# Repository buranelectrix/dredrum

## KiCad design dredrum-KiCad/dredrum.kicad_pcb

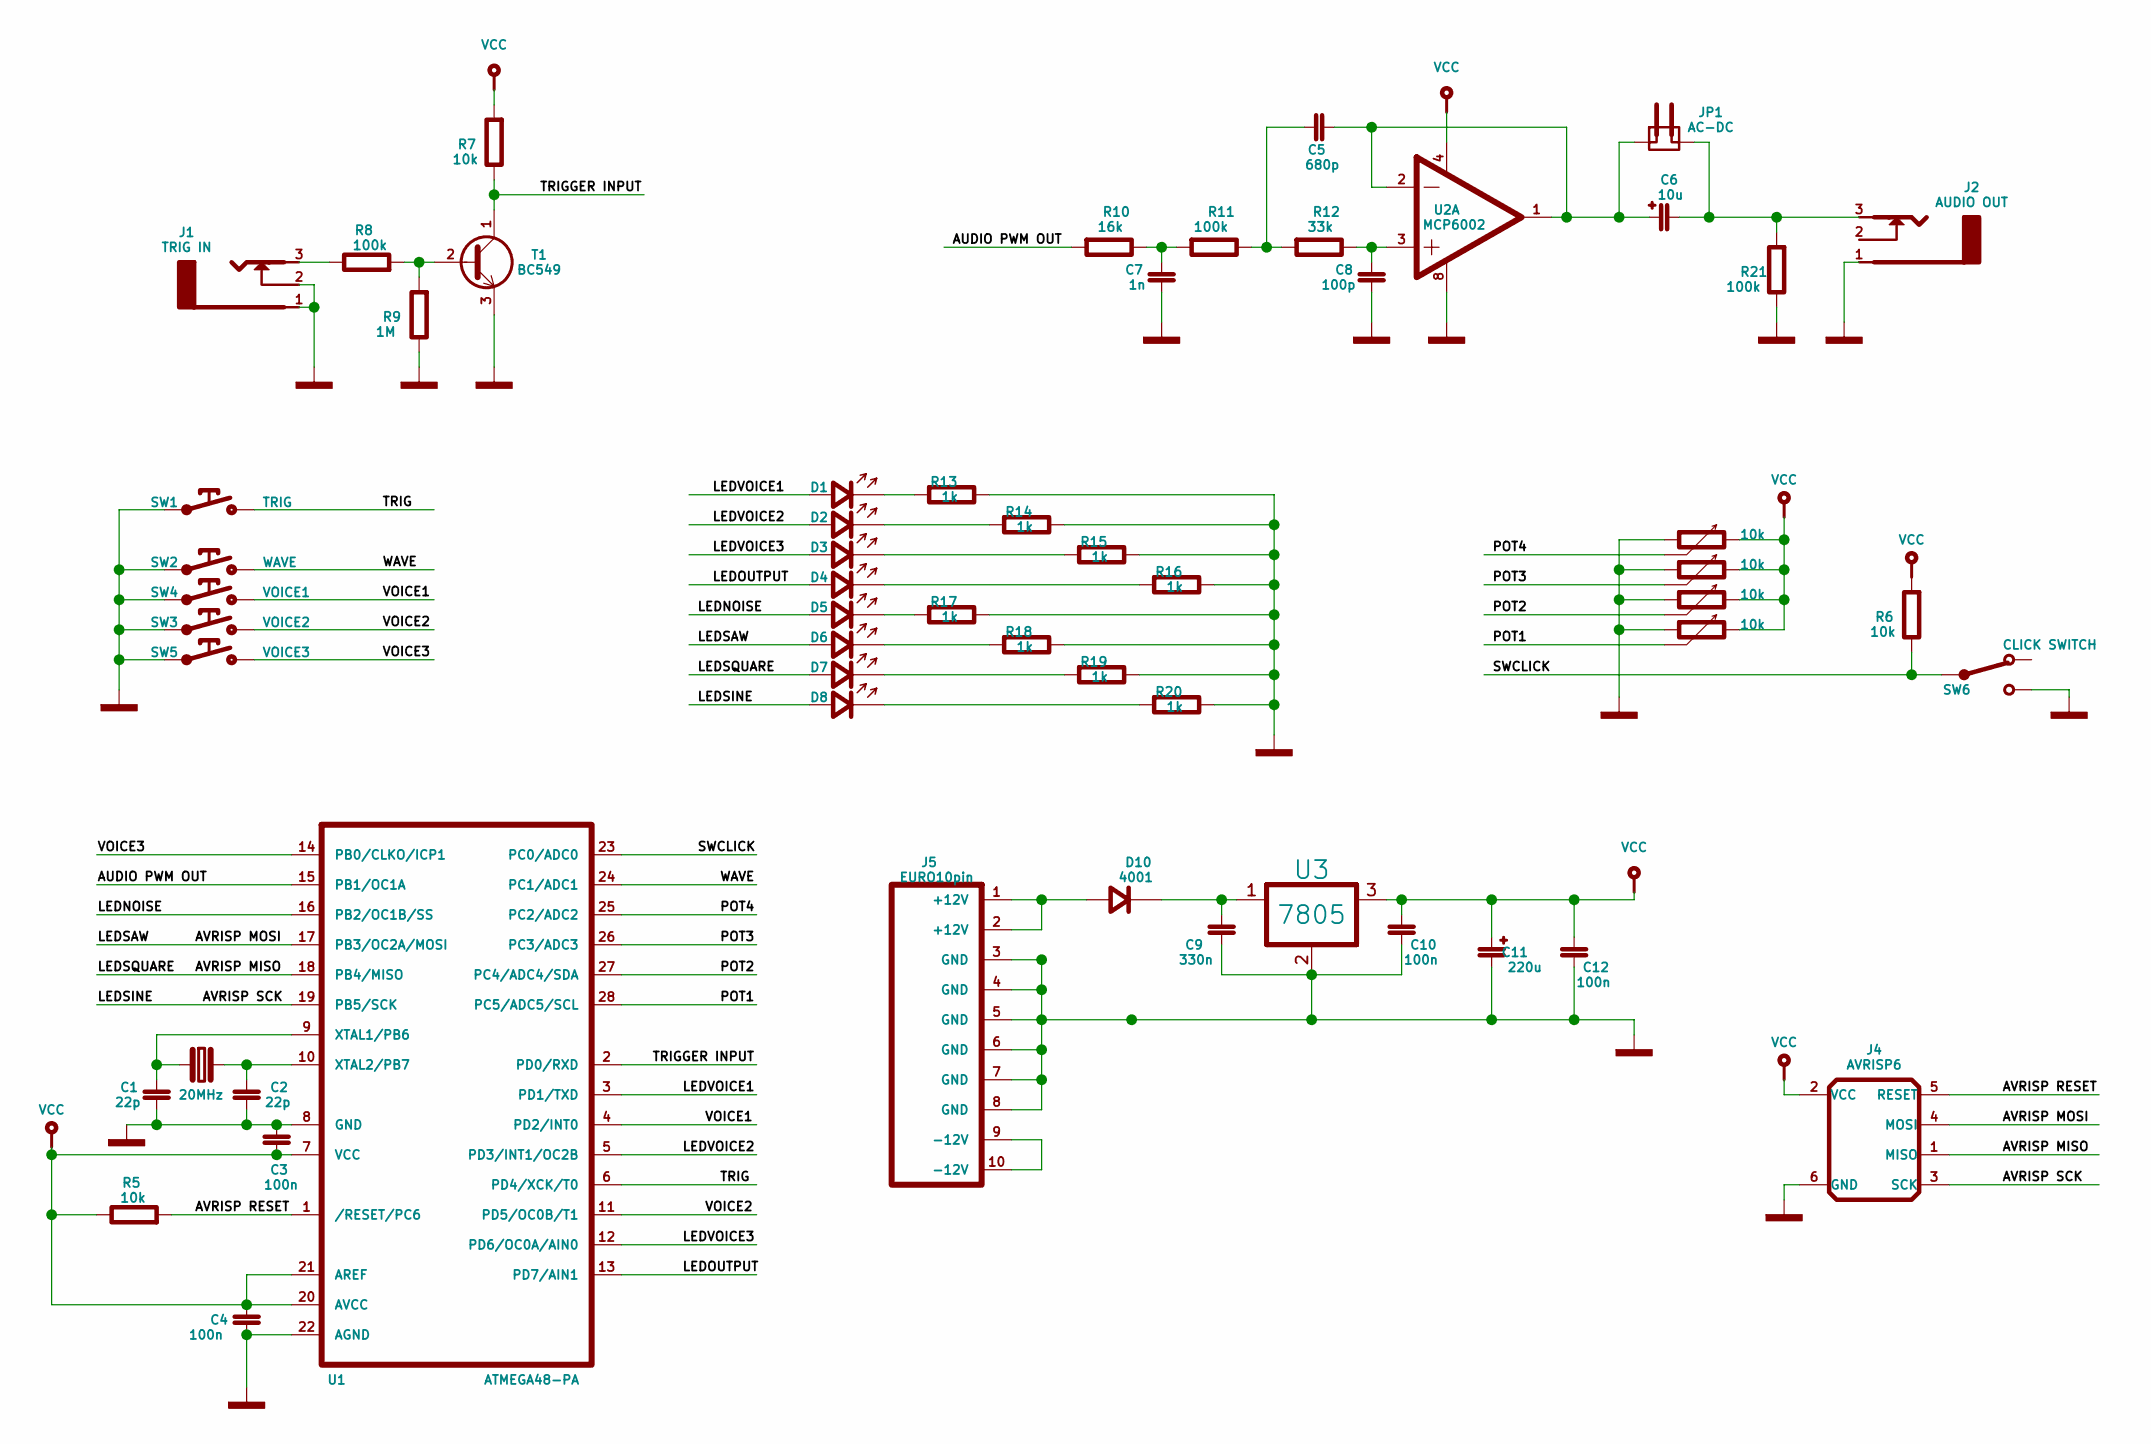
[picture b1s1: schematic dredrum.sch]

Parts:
C1, C2: 22p
C3, C4, C10, C12: 100n
C5: 680p
C6: 10u
C7: 1n
C8: 100p
C9: 330n
C11: 220u
D1: VOICE1
D2: VOICE2
D3: VOICE3
D4: OUTPUT
D5: NOISE
D6: SAW
D7: SQUARE
D8: SINE
D10: 4001
J1: TRIG IN
J2: AUDIO OUT
J4: AVRISP6
J5: EURO10pin
JP1: AC-DC
R1, R2, R3, R4, R5, R6, R7: 10k
R8, R11, R21: 100k
R9: 1M
R10: 16k
R12: 33k
R13, R14, R15, R16, R17, R18, R19, R20: 1k
SW1: TRIG
SW2: WAVE
SW3: VOICE2
SW4: VOICE1
SW5: VOICE3
SW6: CLICK SWITCH
T1: BC549
U1: ATMEGA48-PA
U2: MCP6002
U3: 7805
X?1: 20MHz

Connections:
/AUDIO PWM OUT: R10.1, U1.15 (PB1/OC1A)
/AVRISP MISO: D7.1, J4.1 (MISO), U1.18 (PB4/MISO)
/AVRISP MOSI: D6.1, J4.4 (MOSI), U1.17 (PB3/OC2A/MOSI)
/AVRISP RESET: J4.5 (RESET), R5.1, U1.1 (/RESET/PC6)
/AVRISP SCK: D8.1, J4.3 (SCK), U1.19 (PB5/SCK)
/LEDNOISE: D5.1, U1.16 (PB2/OC1B/SS)
/LEDOUTPUT: D4.1, U1.13 (PD7/AIN1)
/LEDVOICE1: D1.1, U1.3 (PD1/TXD)
/LEDVOICE2: D2.1, U1.5 (PD3/INT1/OC2B)
/LEDVOICE3: D3.1, U1.12 (PD6/OC0A/AIN0)
/POT1: R1.2, U1.28 (PC5/ADC5/SCL)
/POT2: R2.2, U1.27 (PC4/ADC4/SDA)
/POT3: R3.2, U1.26 (PC3/ADC3)
/POT4: R4.2, U1.25 (PC2/ADC2)
/SWCLICK: R6.2, SW6.2, U1.23 (PC0/ADC0)
/TRIG: SW1.2, U1.6 (PD4/XCK/T0)
/TRIGGER INPUT: R7.2, T1.1, U1.2 (PD0/RXD)
/VOICE1: SW4.2, U1.4 (PD2/INT0)
/VOICE2: SW3.2, U1.11 (PD5/OC0B/T1)
/VOICE3: SW5.2, U1.14 (PB0/CLKO/ICP1)
/WAVE: SW2.2, U1.24 (PC1/ADC1)
unnamed: D4.2, R16.1
unnamed: J1.3 (TIP), R8.2
unnamed: C9.2, D10.2, U3.1 (IN)
unnamed: D10.1, J5.1 (+12V), J5.2 (+12V)
unnamed: J5.9 (-12V), J5.10 (-12V)
unnamed: C1.2, U1.9 (XTAL1/PB6), X?1.1
unnamed: C2.2, U1.10 (XTAL2/PB7), X?1.2
unnamed: D8.2, R20.1
unnamed: D7.2, R19.1
unnamed: D6.2, R18.1
unnamed: D5.2, R17.1
unnamed: D3.2, R15.1
unnamed: D2.2, R14.1
unnamed: D1.2, R13.1
unnamed: C6.2, J2.3 (TIP), JP1.2, R21.1
unnamed: C5.2, C6.1, JP1.1, U2.1, U2.2
unnamed: R8.1, R9.1, T1.2
unnamed: C5.1, R11.2, R12.1
unnamed: C8.2, R12.2, U2.3
unnamed: C7.2, R10.2, R11.1

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
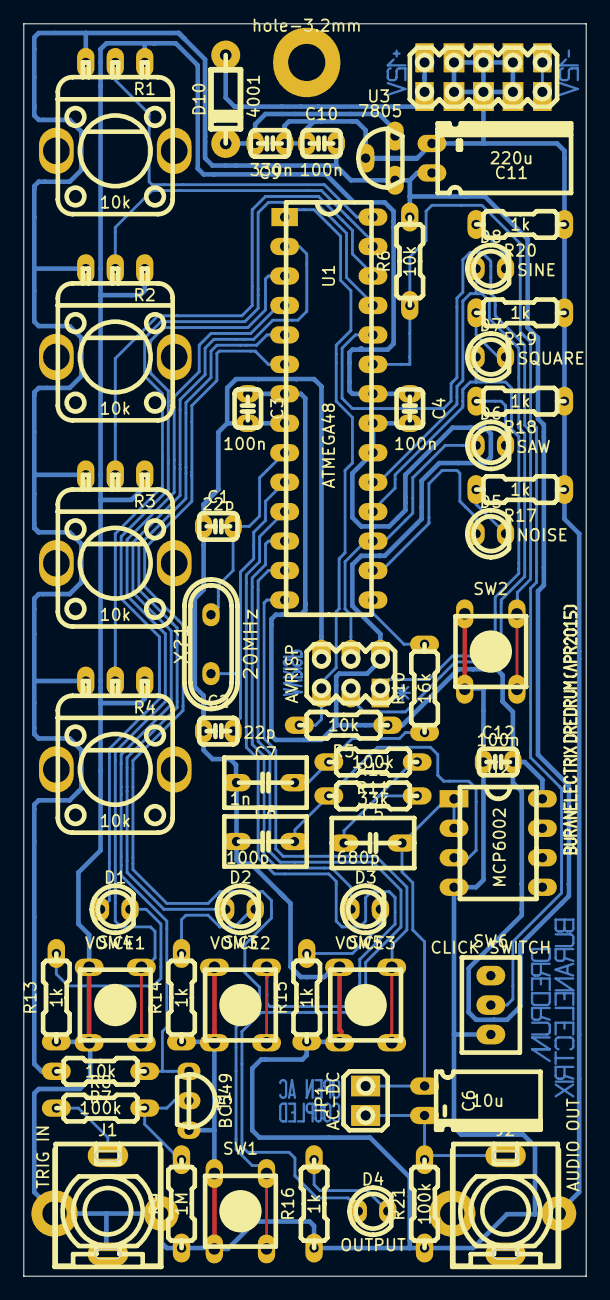
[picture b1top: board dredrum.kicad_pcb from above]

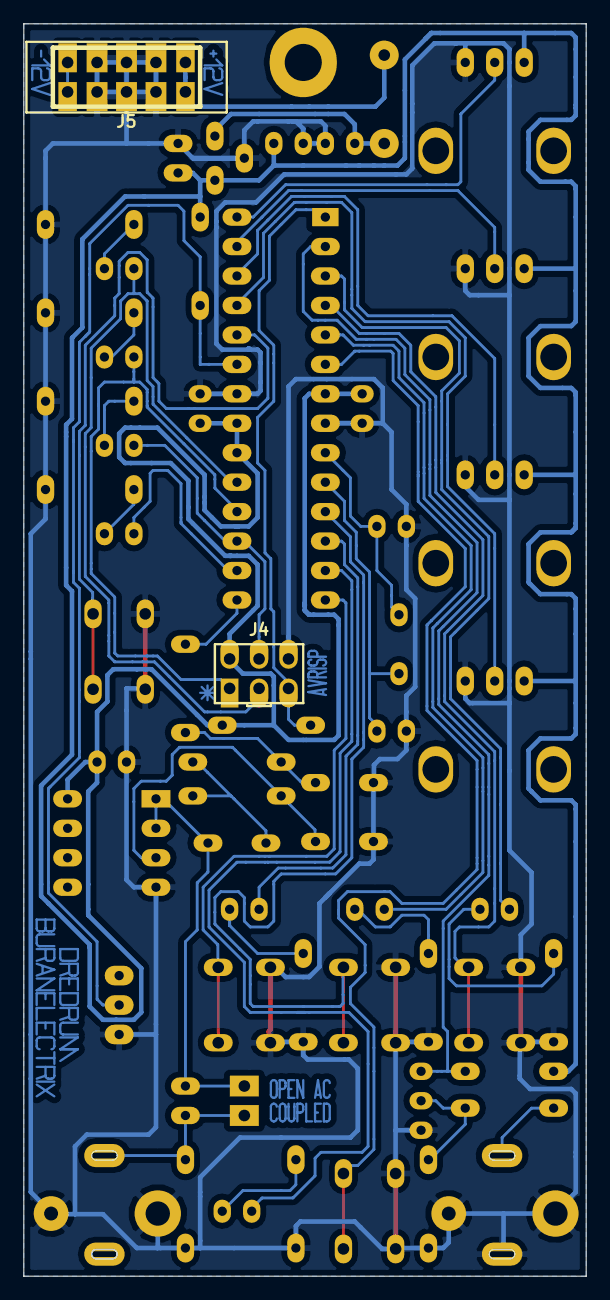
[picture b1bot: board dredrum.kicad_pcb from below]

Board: 2 copper layers, 48.5 x 108.0 mm, 59 parts (2 on the bottom side), 43 nets.

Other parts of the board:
hole-3.2mm: VAL**; hole-circ-3.2mm

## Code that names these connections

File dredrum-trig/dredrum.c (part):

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	#define PITCHENV		2 	//	PITCH DROP	
	#define DECAY		1 	//	DECAY
	#define LEVEL		0 	//	LEVEL
	#define WAVE		4 	//	WAVE

	#define NEW			0
	#define STORE		1
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	DDRD = 0x00;
	PORTD = 0x00;

	DDRD &= ~(1 << PD0);	// trig in input
	DDRD |=  (1 << PD1);	// led voice 1 output
	DDRD &= ~(1 << PD2);	// voice 1 button input
	PORTD |= (1 << PD2);	// pullup on
	DDRD |=  (1 << PD3); 	// led voice 2 output
	DDRD &= ~(1 << PD4); 	// trig button input
	PORTD |= (1 << PD4);	// pullup on
	DDRD &= ~(1 << PD5); 	// voice 2 button input
	PORTD |= (1 << PD5);	// pullup on
	DDRD |=  (1 << PD6); 	// led voice 3 output
	DDRD |=  (1 << PD7);	// led play output

	DDRB = 0x00;
	PORTB = 0x00;
	DDRB &= ~(1 << PB0);	// boice 3 button input
	PORTB |= (1 << PB0); 	// pullup on
	DDRB |= (1 << PB1);	// pwm out OC1A
	DDRB |= (1 << PB2);	// leds wave select
	DDRB |= (1 << PB3);
	DDRB |= (1 << PB4);
	DDRB |= (1 << PB5);

	DDRC = 0x00;		// all inputs
	PORTC = 0x00;
	PORTC |= (1 << PC1); 	// wave button pullup

	// internal ADC setup
	ADCSRA |= (1 << ADPS2) | (1 << ADPS1) | (1 << ADPS0); 	//  prescaler 128
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	for (c = 1; c < 7; c++) {
		for (d = 0; d < 100000; d++) {
			if (c & 0x01) {
				PORTD |= (1 << PD1) | (1 << PD3) | (1 << PD6);
			} else {
				PORTD &= ~(1 << PD1);
				PORTD &= ~(1 << PD3);
				PORTD &= ~(1 << PD6);
			}
		}
	}
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
		// LEDS output
		if (voice == 0) {
			PORTD |= (1 << PD1);
			PORTD &= ~(1 << PD3);
			PORTD &= ~(1 << PD6);
		} else if (voice == 1) {
			PORTD &= ~(1 << PD1);
			PORTD |= (1 << PD3);
			PORTD &= ~(1 << PD6);
		} else if (voice == 2) {
			PORTD &= ~(1 << PD1);
			PORTD &= ~(1 << PD3);
			PORTD |= (1 << PD6);
		}

		uint8_t waveleds = 0;
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		last_waveleds = waveleds;

		if ( (v1.playing) || (v2.playing) || (v3.playing) ) {
			PORTD |= (1 << PD7);
		} else {
			PORTD &= ~(1 << PD7);
		}

		// scan and process buttons
			if (TCNT2 > 195) { 			// cca 100Hz
			TCNT2 = 0;

			if (PINC & (1 << PC0)) {
				click_mode = 0;
			} else {
				click_mode = 1;
			}

			buttons.scanned = 0x00;
			if (PIND & (1 << PD4)) buttons.scanned |= (BUTTRIG);
			if (PINC & (1 << PC1)) buttons.scanned |= (BUTWAVE);
			if (PIND & (1 << PD2)) buttons.scanned |= (BUTVOICE1);
			if (PIND & (1 << PD5)) buttons.scanned |= (BUTVOICE2);
			if (PINB & (1 << PB0)) buttons.scanned |= (BUTVOICE3);

			buttons.scanned ^= 0xff;
			buttons.notused |= buttons.scanned & ~(buttons.last);
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			}
			if (freshbutt & BUTWAVE) {
				++ voice_params[voice][WAVE];
				if (voice_params[voice][WAVE] > 3) voice_params[voice][WAVE] = 0;
				buttons.notused &= ~(BUTWAVE);
			}
			if (freshbutt & BUTTRIG) {
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
	static uint8_t triginput = 0;
	triginput <<= 1;
	if (PIND & (1 << PD0)) {} else {triginput |= 0x01;}
	if ((triginput & 0x03) == 0x01) {trigger = 1;}
}

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
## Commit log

2015-05-09 original late spring commit

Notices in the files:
dredrum-trig/dredrum.c:
Copyright 2014 Jan Cumpelik
This program is free software: you can redistribute it and/or modify
it under the terms of the GNU General Public License as published by
the Free Software Foundation, either version 3 of the License, or
(at your option) any later version.
dredrum-KiCad/dredrum.kicad_pcb:
this PCB design is released under cc-by-sa 3.0 license
dredrum-KiCad/dredrum.sch:
this schematic is released under cc-by-sa 3.0 license
